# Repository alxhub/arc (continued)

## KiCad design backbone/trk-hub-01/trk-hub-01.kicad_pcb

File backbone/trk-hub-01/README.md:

# ARC-TRK-HUB-01

ARC-TRK-HUB-01 connects the ARC backbone to trackside devices. It receives commands over CAN and manages three separate LIN runs. Each run can serve signal and accessory nodes along the track and can be switched independently.

The hub has its own connection to the layout's supply. It measures the power sent down its LIN runs, so the controller can see their combined load. A status light and an expansion port are available at the hub.

The CAN backbone crosses an electrical isolation boundary here. The shorter LIN runs share the hub's local power and return.

[Board design](board.kdl)
[PCB layout](trk-hub-01.kicad_pcb)

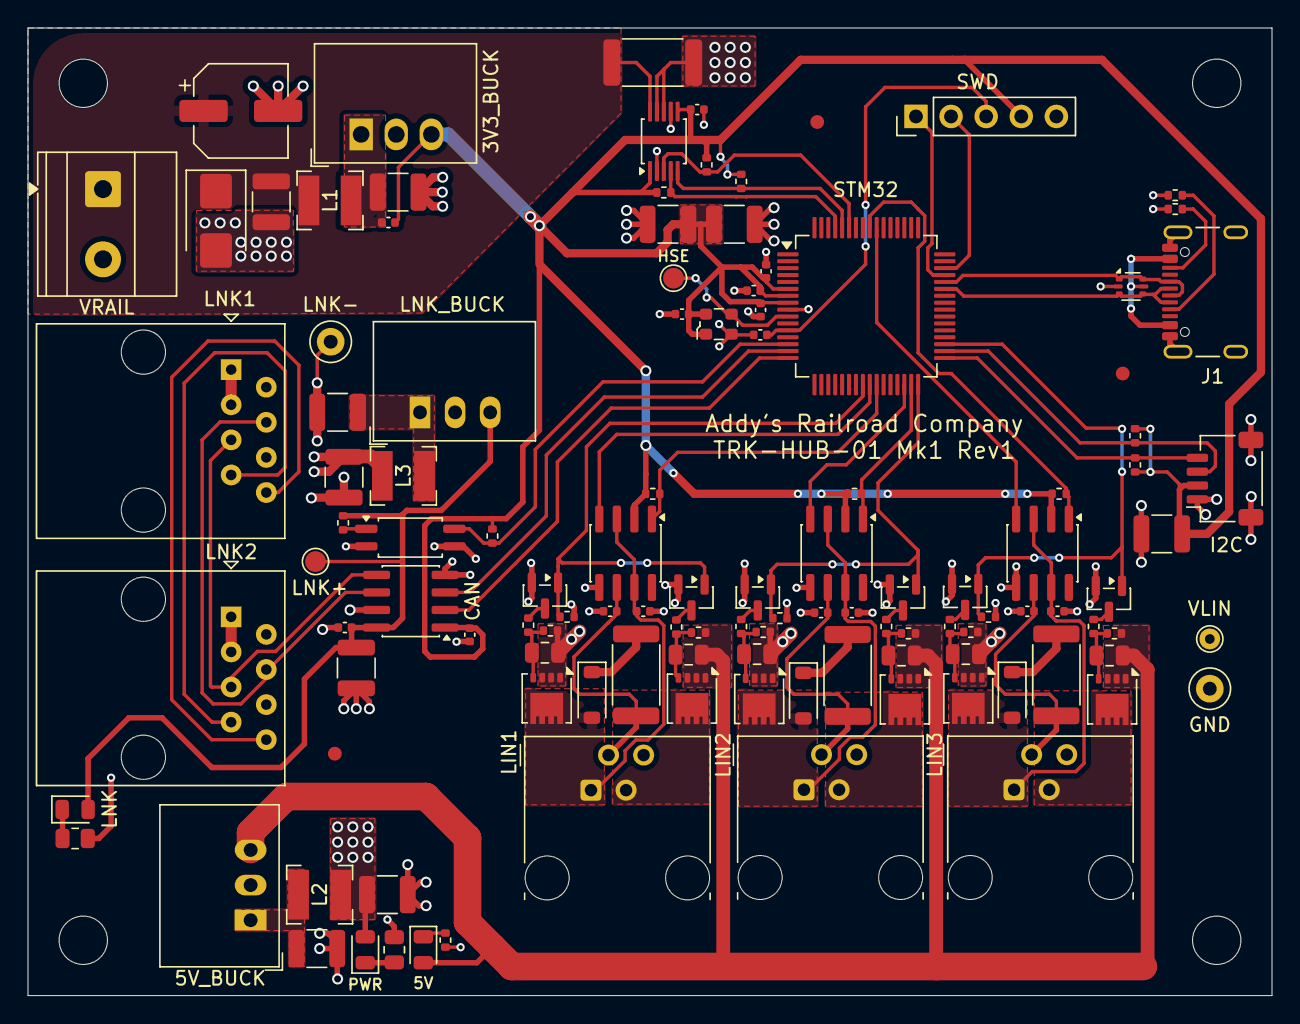
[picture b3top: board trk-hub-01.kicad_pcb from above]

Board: 4 copper layers, 90.0 x 70.0 mm, 121 parts (0 on the bottom side), 69 nets.

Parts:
3V3_BUCK: R-78K3.3-0.5; Converter_DCDC_RECOM_R-78K-0.5_THT
5V: green; LED_0805_2012Metric
5V_BUCK: R-78E5.0-0.5; Converter_DCDC_RECOM_R-78E-0.5_THT
C1: 47µF; CP_Elec_6.3x7.7
C2, C10, C14, C18, C22, C23, C25, C27, C28, C30, C31: 100nF; C_0402_1005Metric
C3, C4, C6, C20, C32: 10µF; C_1210_3225Metric
C5, C11, C15, C19: 1nF; C_0402_1005Metric
C7, C21, C24, C26: 4.7µF; C_1210_3225Metric
C8, C9, C12, C13, C16, C17: 1µF; C_0805_2012Metric
C29: 1µF; C_1210_3225Metric
CAN: ISO1044BD; SOIC-8_3.9x4.9mm_P1.27mm
D1: SMBJ18A; D_SMB
D2, D3, D4: 1N4148W; D_SOD-123
FID1, FID2, FID3: Fiducial; Fiducial_1mm_Mask2mm
GND: TestPoint; TestPoint_Loop_D2.50mm_Drill1.0mm
H1, H2, H3, H4: MountingHole; MountingHole_3.5mm
HSE: TestPoint; TestPoint_Pad_D1.5mm
I2C: Conn_01x04_MountingPin; JST_SH_SM04B-SRSS-TB_1x04-1MP_P1.00mm_Horizontal
J1: USB_C_Receptacle_USB2.0_16P; USB_C_Receptacle_GCT_USB4105-xx-A_16P_TopMnt_Horizontal
L1: 100µH; L_Bourns-SRN4018
L2, L3: 15µH; L_Bourns-SRN4018
LIN1, LIN2, LIN3: RJ11; RJ11_Stewart_SS-90000-006_Horizontal
LNK: green; LED_0805_2012Metric
LNK1, LNK2: RJ45; RJ45_Amphenol_54602-x08_Horizontal
LNK+: TestPoint; TestPoint_Pad_D1.5mm
LNK-: TestPoint; TestPoint_Loop_D2.50mm_Drill1.0mm
LNK_BUCK: R-78E5.0-0.5; Converter_DCDC_RECOM_R-78E-0.5_THT
MON: INA226; TSSOP-10_3x3mm_P0.5mm
PWR: green; LED_0805_2012Metric
Q1, Q3, Q5, Q7, Q9, Q11: DMP3013SFV; Diodes_PowerDI3333-8
Q2, Q4, Q6, Q8, Q10, Q12: BSS138; SOT-23
R1: 20mΩ; R_2512_6332Metric
R2: 1kΩ; R_0402_1005Metric
R3: 5.1kΩ; R_0805_2012Metric
R4: 300Ω; R_0402_1005Metric
R5, R8, R12, R15, R19, R22: 49.9kΩ; R_0402_1005Metric
R6, R9, R13, R16, R20, R23, R29, R30: 5.1kΩ; R_0402_1005Metric
R7, R14, R21, R28: 100kΩ; R_0402_1005Metric
R10, R17, R24: 10kΩ; R_0402_1005Metric
R11, R18, R25: 1kΩ; R_2512_6332Metric
R26: 300Ω; R_0805_2012Metric
R27: 2kΩ; R_0402_1005Metric
R31, R32, R33, R34: 4.7kΩ; R_0402_1005Metric
STM32: STM32G0B1RETx; LQFP-64_10x10mm_P0.5mm
SWD: Conn_01x05; PinHeader_1x05_P2.54mm_Vertical
U1, U2, U3: NCV7321D12R2G; SOIC-8_3.9x4.9mm_P1.27mm
U4: FODM217A; SOP-4_4.4x2.6mm_P1.27mm
U5: USBLC6-2P6; SOT-666
VLIN: TestPoint; TestPoint_THTPad_D1.5mm_Drill0.7mm
VRAIL: Conn_01x02; TerminalBlock_Phoenix_MKDS-1,5-2-5.08_1x02_P5.08mm_Horizont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
Y1: 40MHz; Oscillator_SMD_ECS_2520MV-xxx-xx-4Pin_2.5x2.0mm

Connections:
3V3: 3V3_BUCK.3, C2.1, C5.2, C22.1, C25.1, C26.1, C28.1, C29.1, C30.1, C31.1, C32.1, CAN.1, I2C.2, MON.1, MON.6, R2.2, R10.2, R17.2, R24.2, R28.2, R31.2, R32.2, R33.2, R34.2, STM32.6, STM32.7, STM32.8, SWD.4, U1.2, U2.2, U3.2, Y1.1, Y1.4
unnamed: 3V3_BUCK.1, C4.1, C5.1, L1.2
unnamed: 5V.1, R4.1
unnamed: 5V_BUCK.1, C7.1, L2.2
unnamed: LNK.1, R26.1
unnamed: C21.1, L3.2, LNK_BUCK.1
unnamed: PWR.1, R3.1
unnamed: R27.2, U4.1
V5: 5V.2, 5V_BUCK.3, C9.2, C13.2, C17.2, Q3.1, Q3.2, Q3.3, Q7.1, Q7.2, Q7.3, Q11.1, Q11.2, Q11.3, R8.2, R15.2, R22.2
VBUS: J1.A4, J1.A9, J1.B4, J1.B9, U5.5
can/rxd: CAN.3, STM32.15
can/txd: CAN.2, STM32.16
expansion/scl: I2C.4, R34.1, STM32.33
expansion/sda: I2C.3, R33.1, STM32.34
hse: HSE.1, STM32.10, Y1.3
leg0/EN: Q2.1, Q4.1, R7.1, STM32.24
leg0/LIN: C11.1, LIN1.2, R11.2, U1.6
leg0/V5: LIN1.3, Q3.5
leg0/VPWR: C10.1, D2.2, LIN1.1, Q1.5, U1.3, U1.7
leg0/rxd: R10.1, STM32.26, U1.1
leg0/switch5/GATE: C9.1, Q3.4, R8.1, R9.2
leg0/switch5/drive: Q4.3, R9.1
leg0/switch/GATE: C8.1, Q1.4, R5.1, R6.2
leg0/switch/drive: Q2.3, R6.1
leg0/term/K: D2.1, R11.1
leg0/txd: STM32.25, U1.4
leg1/EN: Q6.1, Q8.1, R14.1, STM32.32
leg1/LIN: C15.1, LIN2.2, R18.2, U2.6
leg1/V5: LIN2.3, Q7.5
leg1/VPWR: C14.1, D3.2, LIN2.1, Q5.5, U2.3, U2.7
leg1/rxd: R17.1, STM32.31, U2.1
leg1/switch5/GATE: C13.1, Q7.4, R15.1, R16.2
leg1/switch5/drive: Q8.3, R16.1
leg1/switch/GATE: C12.1, Q5.4, R12.1, R13.2
leg1/switch/drive: Q6.3, R13.1
leg1/term/K: D3.1, R18.1
leg1/txd: STM32.30, U2.4
leg2/EN: Q10.1, Q12.1, R21.1, STM32.35
leg2/LIN: C19.1, LIN3.2, R25.2, U3.6
leg2/V5: LIN3.3, Q11.5
leg2/VPWR: C18.1, D4.2, LIN3.1, Q9.5, U3.3, U3.7
leg2/rxd: R24.1, STM32.56, U3.1
leg2/switch5/GATE: C17.1, Q11.4, R22.1, R23.2
leg2/switch5/drive: Q12.3, R23.1
leg2/switch/GATE: C16.1, Q9.4, R19.1, R20.2
leg2/switch/drive: Q10.3, R20.1
leg2/term/K: D4.1, R25.1
leg2/txd: STM32.55, U3.4
link/V5_LINK: C23.1, C24.1, CAN.8, LNK.2, LNK+.1, LNK_BUCK.3, R27.1
link/VLINK: C20.1, L3.1, LNK1.1, LNK1.3, LNK2.1, LNK2.3
link/VLINK_GND: C20.2, C21.2, C23.2, C24.2, CAN.7, LNK1.2, LNK1.6, LNK2.2, LNK2.6, LNK-.1, LNK_BUCK.2, R26.2, U4.2
link/good: R28.1, STM32.14, U4.4
link/jacks/CANH: CAN.6, LNK1.4, LNK2.4
link/jacks/CANL: CAN.5, LNK1.5, LNK2.5
link/jacks/DCC_A: LNK1.7, LNK2.7
link/jacks/DCC_B: LNK1.8, LNK2.8
monitor/scl: MON.5, R32.1, STM32.60
monitor/sda: MON.4, R31.1, STM32.61
nALERT: MON.3, R2.1, STM32.59
nrst: C27.1, STM32.12, SWD.3
rail/GND: 3V3_BUCK.2, 5V_BUCK.2, C1.2, C2.2, C3.2, C4.2, C6.2, C7.2, C10.2, C11.2, C14.2, C15.2, C18.2, C19.2, C22.2, C25.2, C26.2, C27.2, C28.2, C29.2, C30.2, C31.2, C32.2, CAN.4, D1.2, GND.1, I2C.1, I2C.MP, J1.A1, J1.A12, J1.B1, J1.B12, J1.SH, LIN1.4, LIN2.4, LIN3.4, MON.2, MON.7, Q2.2, Q4.2, Q6.2, Q8.2, Q10.2, Q12.2, R3.2, R4.2, R7.2, R14.2, R21.2, R29.2, R30.2, STM32.9, SWD.5, U1.5, U2.5, U3.5, U4.3, U5.2, VRAIL.2, Y1.2
rail/VLIN: C6.1, C8.2, C12.2, C16.2, L2.1, MON.8, MON.9, PWR.2, Q1.1, Q1.2, Q1.3, Q5.1, Q5.2, Q5.3, Q9.1, Q9.2, Q9.3, R1.2, R5.2, R12.2, R19.2, VLIN.1
rail/VPWR: C1.1, C3.1, D1.1, L1.1, MON.10, R1.1, VRAIL.1
swd/swclk: STM32.46, SWD.2
swd/swdio: STM32.45, SWD.1
usb/cc1: J1.A5, R29.1
usb/cc2: J1.B5, R30.1
usb/d+: J1.A6, J1.B6, STM32.44, U5.1, U5.6
usb/d-: J1.A7, J1.B7, STM32.43, U5.3, U5.4

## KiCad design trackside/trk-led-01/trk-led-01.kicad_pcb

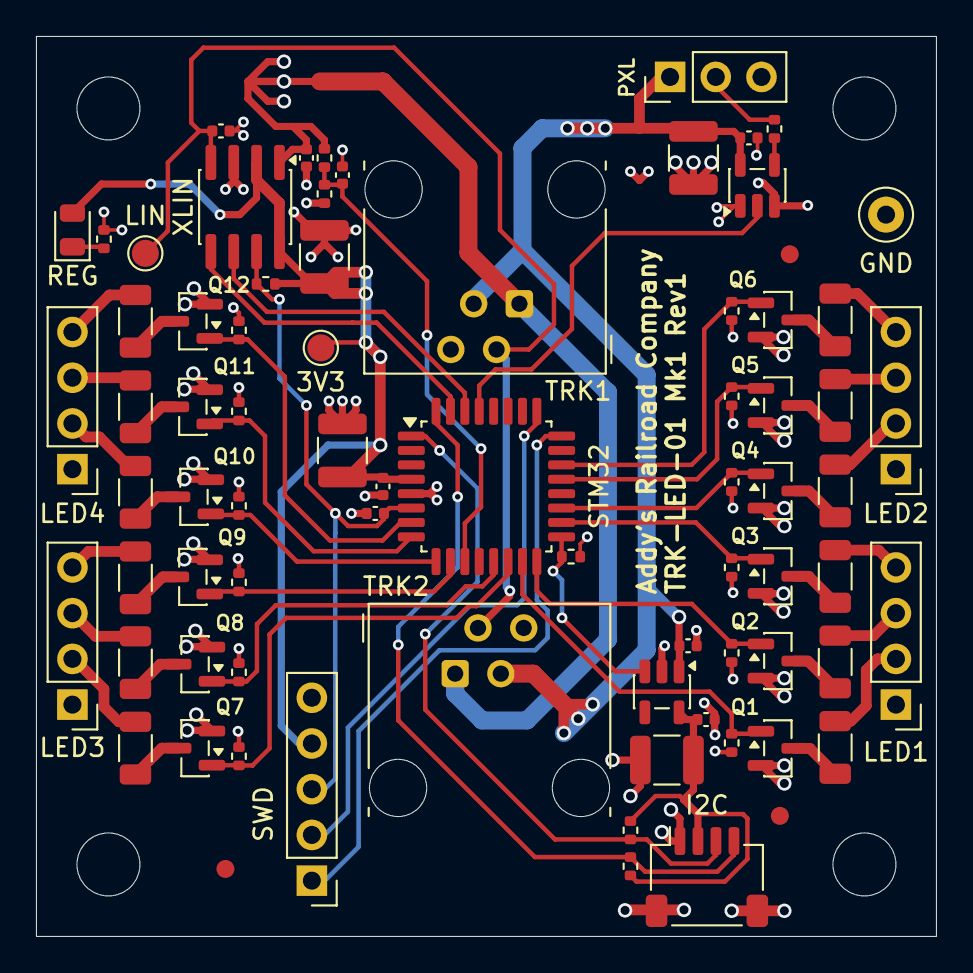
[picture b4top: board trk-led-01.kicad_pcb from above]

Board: 4 copper layers, 50.0 x 50.0 mm, 80 parts (0 on the bottom side), 55 nets.

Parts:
3V3: TestPoint; TestPoint_Pad_D1.5mm
C1, C4, C6, C7, C9: 100nF; C_0402_1005Metric
C2, C5, C12: 10µF; C_1210_3225Metric
C3: 220pF; C_0402_1005Metric
C8: 4.7µF; C_1210_3225Metric
C10, C11: 1µF; C_0402_1005Metric
FID1, FID2, FID3: Fiducial; Fiducial_1mm_Mask2mm
GND: TestPoint; TestPoint_Loop_D2.50mm_Drill1.0mm
H1, H2, H3, H4: MountingHole; MountingHole_3.5mm
I2C: Conn_01x04_MountingPin; JST_SH_SM04B-SRSS-TB_1x04-1MP_P1.00mm_Horizontal
LED1, LED2, LED3, LED4: Conn_01x04; PinHeader_1x04_P2.54mm_Vertical
LIN: TestPoint; TestPoint_Pad_D1.5mm
PXL: Conn_01x03; PinHeader_1x03_P2.54mm_Vertical
Q1, Q2, Q3, Q4, Q5, Q6, Q7, Q8, Q9, Q10, Q11, Q12: DMN3404L; SOT-23
R1: 10kΩ; R_0402_1005Metric
R2: 330Ω; R_0402_1005Metric
R3, R5, R7, R9, R11, R13, R15, R17, R19, R21, R23, R25, R27, R30: 100kΩ; R_0402_1005Metric
R4, R6, R8, R10, R12, R14, R16, R18, R20, R22, R24, R26: 4.3kΩ; R_1206_3216Metric
R28: 18kΩ; R_0402_1005Metric
R29: 680Ω; R_0402_1005Metric
R31, R32: 4.7kΩ; R_0402_1005Metric
REG: green; LED_0805_2012Metric
STM32: STM32C092KBTx; LQFP-32_7x7mm_P0.8mm
SWD: Conn_01x05; PinHeader_1x05_P2.54mm_Vertical
TRK1, TRK2: RJ11; RJ11_Stewart_SS-90000-006_Horizontal
U1: 74AHCT1G125; SOT-23-5
U2: AP2112K-3.3; SOT-23-5
XLIN: NCV7428D13R2G; SOIC-8_3.9x4.9mm_P1.27mm

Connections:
unnamed: R29.1, REG.1
unnamed: R2.1, U1.4
unnamed: R30.1, STM32.17, U2.3
debug/swd.swclk: STM32.25, SWD.2
debug/swd.swdio: STM32.24, SWD.1
expansion/pulls/i2c.scl: I2C.4, R32.1, STM32.32
expansion/pulls/i2c.sda: I2C.3, R31.1, STM32.1
expansion/pulls/rail.rail: C11.1, C12.1, I2C.2, R31.2, R32.2, U2.5
head1/K1: LED1.2, R4.2
head1/K2: LED1.3, R6.2
head1/K3: LED1.4, R8.2
head1/gates.l1: Q1.1, R3.1, STM32.15
head1/gates.l2: Q2.1, R5.1, STM32.16
head1/gates.l3: Q3.1, R7.1, STM32.18
head1/l1/drain: Q1.3, R4.1
head1/l2/drain: Q2.3, R6.1
head1/l3/drain: Q3.3, R8.1
head2/K1: LED2.2, R10.2
head2/K2: LED2.3, R12.2
head2/K3: LED2.4, R14.2
head2/gates.l1: Q4.1, R9.1, STM32.19
head2/gates.l2: Q5.1, R11.1, STM32.21
head2/gates.l3: Q6.1, R13.1, STM32.22
head2/l1/drain: Q4.3, R10.1
head2/l2/drain: Q5.3, R12.1
head2/l3/drain: Q6.3, R14.1
head3/K1: LED3.2, R16.2
head3/K2: LED3.3, R18.2
head3/K3: LED3.4, R20.2
head3/gates.l1: Q7.1, R15.1, STM32.14
head3/gates.l2: Q8.1, R17.1, STM32.13
head3/gates.l3: Q9.1, R19.1, STM32.10
head3/l1/drain: Q7.3, R16.1
head3/l2/drain: Q8.3, R18.1
head3/l3/drain: Q9.3, R20.1
head4/K1: LED4.2, R22.2
head4/K2: LED4.3, R24.2
head4/K3: LED4.4, R26.2
head4/gates.l1: Q10.1, R21.1, STM32.9
head4/gates.l2: Q11.1, R23.1, STM32.8
head4/gates.l3: Q12.1, R25.1, STM32.7
head4/l1/drain: Q10.3, R22.1
head4/l2/drain: Q11.3, R24.1
head4/l3/drain: Q12.3, R26.1
node/GND: C1.2, C2.2, C3.2, C4.2, C5.2, C6.2, C7.2, C8.2, C9.2, C10.2, C11.2, C12.2, GND.1, I2C.1, I2C.MP, PXL.3, Q1.2, Q2.2, Q3.2, Q4.2, Q5.2, Q6.2, Q7.2, Q8.2, Q9.2, Q10.2, Q11.2, Q12.2, R3.2, R5.2, R7.2, R9.2, R11.2, R13.2, R15.2, R17.2, R19.2, R21.2, R23.2, R25.2, R28.2, R29.2, R30.2, STM32.5, SWD.5, TRK1.4, TRK2.4, U1.1, U1.3, U2.2, XLIN.3
node/LIN: C3.1, LIN.1, TRK1.2, TRK2.2, XLIN.4
node/V5: C4.1, C5.1, C10.1, PXL.1, TRK1.3, TRK2.3, U1.5, U2.1
node/VPWR: C1.1, LED1.1, LED2.1, LED3.1, LED4.1, R27.1, TRK1.1, TRK2.1, XLIN.1
node/link.rx: STM32.30, XLIN.6
node/link.tx: STM32.31, XLIN.5
node/v3v3.rail: 3V3.1, C2.1, C7.1, C8.1, R1.2, REG.2, STM32.4, SWD.4, XLIN.2, XLIN.8
nrst: C9.1, R1.1, STM32.6, SWD.3, XLIN.7
pixels/DOUT: PXL.2, R2.2
pixels/data: STM32.29, U1.2
sense/tap: C6.1, R27.2, R28.1, STM32.11

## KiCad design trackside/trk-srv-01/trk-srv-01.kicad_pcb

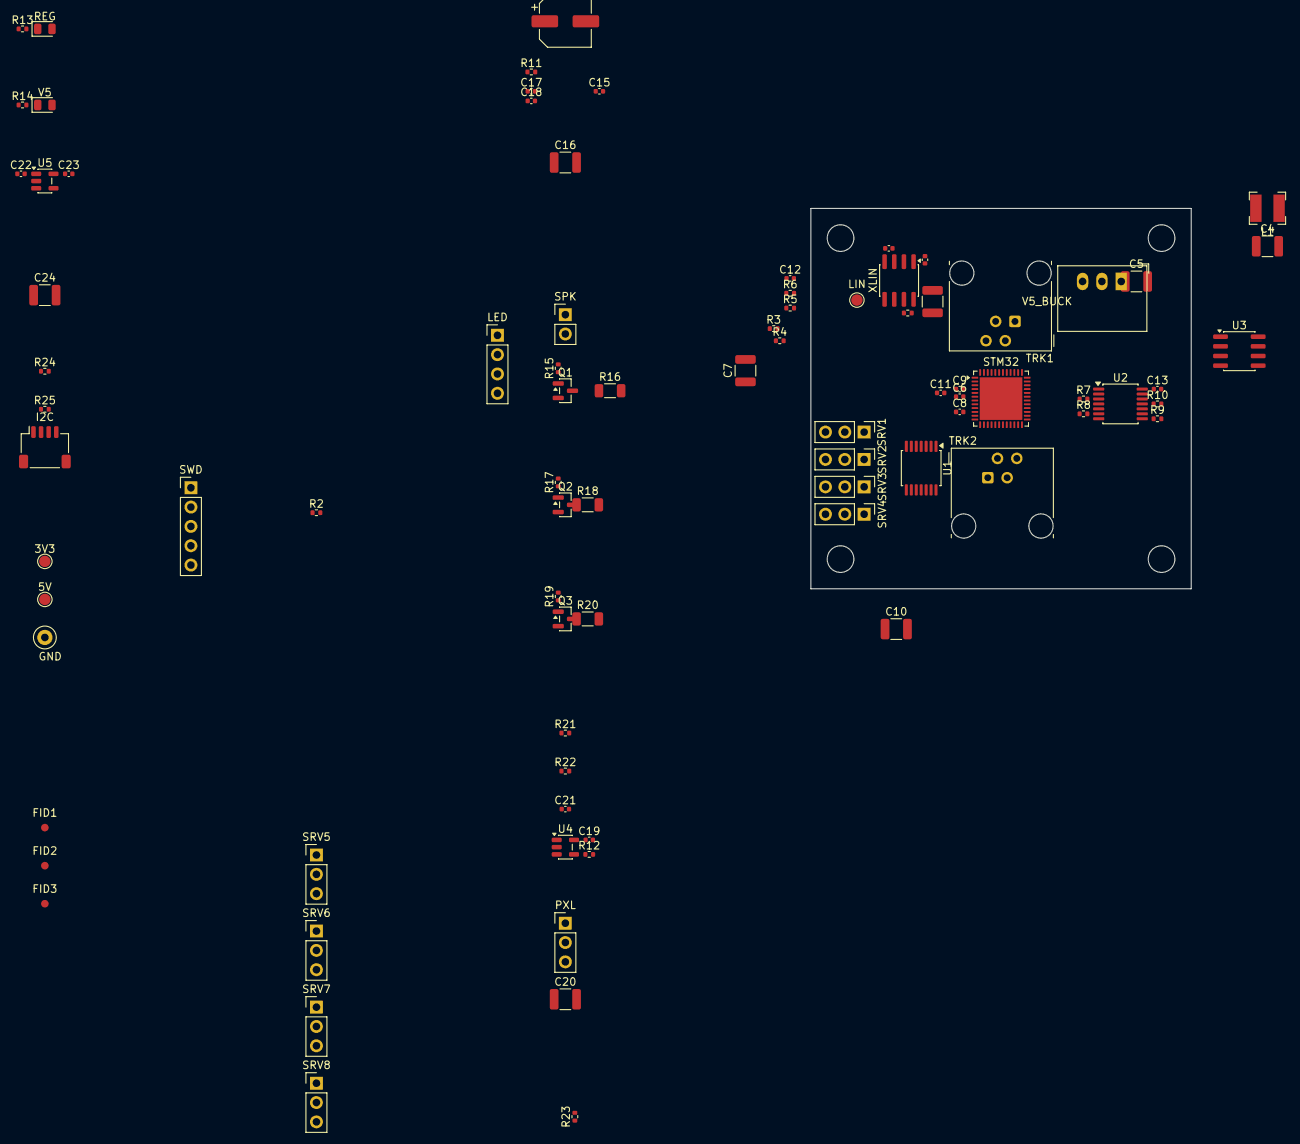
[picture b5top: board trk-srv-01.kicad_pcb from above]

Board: 2 copper layers, 50.0 x 50.0 mm, 89 parts (0 on the bottom side), 54 nets, no tracks yet.

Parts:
3V3, 5V: TestPoint; TestPoint_Pad_D1.5mm
C1, C6, C8, C9, C11, C12, C13, C17, C18, C19, C21: 100nF; C_0402_1005Metric
C2, C4, C5, C16, C20, C24: 10µF; C_1210_3225Metric
C3: 220pF; C_0402_1005Metric
C7: 4.7µF; C_1210_3225Metric
C10: 1µF; C_1210_3225Metric
C14: 100µF; CP_Elec_6.3x5.8
C15, C22, C23: 1µF; C_0402_1005Metric
FID1, FID2, FID3: Fiducial; Fiducial_1mm_Mask2mm
GND: TestPoint; TestPoint_Loop_D2.50mm_Drill1.0mm
H1, H2, H3, H4: MountingHole; MountingHole_3.5mm
I2C: Conn_01x04_MountingPin; JST_SH_SM04B-SRSS-TB_1x04-1MP_P1.00mm_Horizontal
L1: 15µH; L_Bourns-SRN4018
LED: Conn_01x04; PinHeader_1x04_P2.54mm_Vertical
LIN: TestPoint; TestPoint_Pad_D1.5mm
PXL: Conn_01x03; PinHeader_1x03_P2.54mm_Vertical
Q1, Q2, Q3: DMN3404L; SOT-23
R1: 10kΩ; R_0402_1005Metric
R2, R3, R4, R5, R6, R7, R8, R9, R10, R11, R15, R17, R19, R21, R23: 100kΩ; R_0402_1005Metric
R12: 330Ω; R_0402_1005Metric
R13: 680Ω; R_0402_1005Metric
R14: 1.5kΩ; R_0402_1005Metric
R16, R18, R20: 4.3kΩ; R_1206_3216Metric
R22: 18kΩ; R_0402_1005Metric
R24, R25: 4.7kΩ; R_0402_1005Metric
REG: green; LED_0805_2012Metric
SPK: Conn_01x02; PinHeader_1x02_P2.54mm_Vertical
SRV1, SRV2, SRV3, SRV4, SRV5, SRV6, SRV7, SRV8: Conn_01x03; PinHeader_1x03_P2.54mm_Vertical
STM32: STM32G0B1CEUx; QFN-48-1EP_7x7mm_P0.5mm_EP5.6x5.6mm
SWD: Conn_01x05; PinHeader_1x05_P2.54mm_Vertical
TRK1, TRK2: RJ11; RJ11_Stewart_SS-90000-006_Horizontal
U1, U2: 74AHCT125; TSSOP-14_4.4x5mm_P0.65mm
U3: PAM8302AAD; SOIC-8_3.9x4.9mm_P1.27mm
U4: 74AHCT1G125; SOT-23-5
U5: AP2112K-3.3; SOT-23-5
V5: green; LED_0805_2012Metric
V5_BUCK: R-78E5.0-1.0; Converter_DCDC_RECOM_R-78E-0.5_THT
XLIN: NCV7428D13R2G; SOIC-8_3.9x4.9mm_P1.27mm

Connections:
unnamed: R13.1, REG.1
unnamed: R3.1, SRV1.1, U1.3
unnamed: R4.1, SRV2.1, U1.6
unnamed: R5.1, SRV3.1, U1.8
unnamed: R6.1, SRV4.1, U1.11
unnamed: R7.1, SRV5.1, U2.3
unnamed: R8.1, SRV6.1, U2.6
unnamed: R9.1, SRV7.1, U2.8
unnamed: R10.1, SRV8.1, U2.11
unnamed: C17.2, U3.3
unnamed: C18.2, U3.4
unnamed: R12.1, U4.4
unnamed: R23.1, STM32.21, U5.3
unnamed: R14.1, V5.1
bell/OUT+: SPK.1, U3.5
bell/OUT-: SPK.2, U3.8
bell/enable: R11.1, STM32.25, U3.1
bell/in: C17.1, STM32.15
expansion/pulls/i2c.scl: I2C.4, R25.1, STM32.47
expansion/pulls/i2c.sda: I2C.3, R24.1, STM32.48
expansion/pulls/rail.rail: C23.1, C24.1, I2C.2, R24.2, R25.2, U5.5
lamp1/drain: Q1.3, R16.1
lamp1/gate: Q1.1, R15.1, STM32.28
lamp2/drain: Q2.3, R18.1
lamp2/gate: Q2.1, R17.1, STM32.29
lamp3/drain: Q3.3, R20.1
lamp3/gate: Q3.1, R19.1, STM32.32
lamps/K1: LED.2, R16.2
lamps/K2: LED.3, R18.2
lamps/K3: LED.4, R20.2
lin/rxd: STM32.46, XLIN.5
lin/txd: STM32.45, XLIN.6
node/GND: C1.2, C2.2, C3.2, C4.2, C5.2, C6.2, C7.2, C8.2, C9.2, C10.2, C11.2, C12.2, C13.2, C14.2, C15.2, C16.2, C18.1, C19.2, C20.2, C21.2, C22.2, C23.2, C24.2, GND.1, I2C.1, I2C.MP, PXL.3, Q1.2, Q2.2, Q3.2, R3.2, R4.2, R5.2, R6.2, R7.2, R8.2, R9.2, R10.2, R11.2, R13.2, R14.2, R15.2, R17.2, R19.2, R22.2, R23.2, SRV1.3, SRV2.3, SRV3.3, SRV4.3, SRV5.3, SRV6.3, SRV7.3, SRV8.3, STM32.7, STM32.49, SWD.5, TRK1.4, TRK2.4, U1.7, U2.7, U3.7, U4.1, U4.3, U5.2, V5_BUCK.2, XLIN.3
node/LIN: C3.1, LIN.1, TRK1.2, TRK2.2, XLIN.4
node/V5: TRK1.3, TRK2.3
node/VPWR: C1.1, C4.1, L1.1, LED.1, R21.1, TRK1.1, TRK2.1, XLIN.1
node/v3v3.rail: 3V3.1, C2.1, C6.1, C7.1, C9.1, C10.1, C11.1, R1.2, REG.2, STM32.4, STM32.5, STM32.6, SWD.4, XLIN.2, XLIN.8
nrst: C8.1, R1.1, STM32.10, SWD.3, XLIN.7
pixels/DOUT: PXL.2, R12.2
pixels/data: STM32.44, U4.2
sense/tap: C21.1, R21.2, R22.1, STM32.22
servos/enable: R2.1, STM32.24, U1.1, U1.4, U1.10, U1.13, U2.1, U2.4, U2.10, U2.13
servos/p1: STM32.11, U1.2
servos/p2: STM32.12, U1.5
servos/p3: STM32.13, U1.9
servos/p4: STM32.14, U1.12
servos/p5: STM32.17, U2.2
servos/p6: STM32.18, U2.5
servos/p7: STM32.19, U2.9
servos/p8: STM32.20, U2.12
swd/swd.swclk: STM32.36, SWD.2
swd/swd.swdio: STM32.35, SWD.1
v5/filtered.rail: C5.1, L1.2, V5_BUCK.1
v5/out.rail: 5V.1, C12.1, C13.1, C14.1, C15.1, C16.1, C19.1, C20.1, C22.1, PXL.1, R2.2, SRV1.2, SRV2.2, SRV3.2, SRV4.2, SRV5.2, SRV6.2, SRV7.2, SRV8.2, U1.14, U2.14, U3.6, U4.5, U5.1, V5.2, V5_BUCK.3

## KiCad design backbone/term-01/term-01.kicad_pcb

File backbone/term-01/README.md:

# ARC-TERM-01

ARC-TERM-01 closes the end of an ARC backbone run. It terminates both the CAN connection used for commands and status and the DCC timing connection used by track drivers. A run uses a terminator at each end; the nodes along it pass the connections through.

The board has one backbone jack. A power light shows whether the backbone supply reaches this end of the run, and measurement points give installers a place to check the supply and both signal pairs.

[Board design](board.kdl)
[PCB layout](term-01.kicad_pcb)

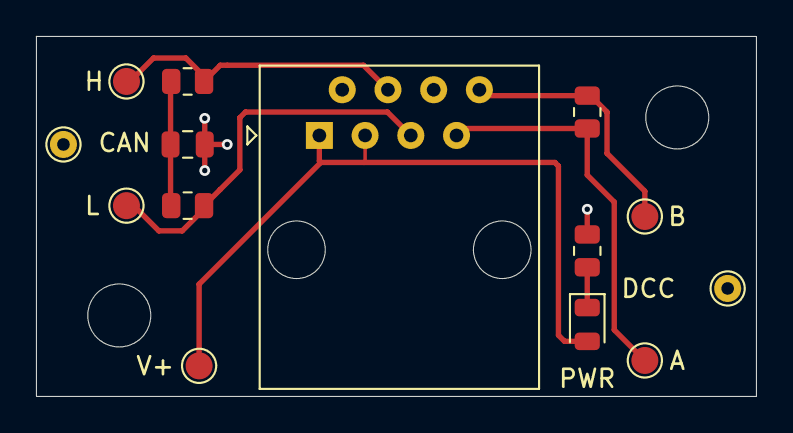
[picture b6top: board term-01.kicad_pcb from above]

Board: 2 copper layers, 40.0 x 20.0 mm, 16 parts (0 on the bottom side), 8 nets.

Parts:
A: TestPoint; TestPoint_Pad_D1.5mm
B: TestPoint; TestPoint_Pad_D1.5mm
C1: 4.7nF; C_0805_2012Metric
H: TestPoint; TestPoint_Pad_D1.5mm
H1, H2: MountingHole; MountingHole_3.5mm
L: TestPoint; TestPoint_Pad_D1.5mm
LNK: RJ45; RJ45_Amphenol_54602-x08_Horizontal
PWR: green; LED_0805_2012Metric
R1, R2: 62Ω; R_0805_2012Metric
R3: 120Ω; R_0805_2012Metric
R4: 5.1kΩ; R_0805_2012Metric
TP1, TP2: TestPoint; TestPoint_THTPad_D1.5mm_Drill0.7mm
V+: TestPoint; TestPoint_Pad_D1.5mm

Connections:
CANH: H.1, LNK.4, R1.1
CANL: L.1, LNK.5, R2.2
CAN_MID: C1.1, R1.2, R2.1
DCC_A: A.1, LNK.7, R3.1
DCC_B: B.1, LNK.8, R3.2
unnamed: PWR.1, R4.1
entry/VLINK: LNK.1, LNK.3, PWR.2, V+.1
entry/VLINK_GND: C1.2, LNK.2, LNK.6, R4.2, TP1.1, TP2.1

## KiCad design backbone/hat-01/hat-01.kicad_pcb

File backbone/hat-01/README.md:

# ARC-HAT-01

ARC-HAT-01 connects a Raspberry Pi to an ARC layout. It powers the Pi from the cabinet's control supply, gives Linux a CAN interface to the backbone, and lets the Pi listen to DCC timing. The Pi controls the layout's master contactor and reads its auxiliary contact to learn whether the contactor closed.

The HAT also exposes the Pi's I²C bus on a Qwiic connector. It keeps the backbone electrically isolated from the Pi and cabinet control wiring.

[Board design](board.kdl)
[PCB layout](hat-01.kicad_pcb)

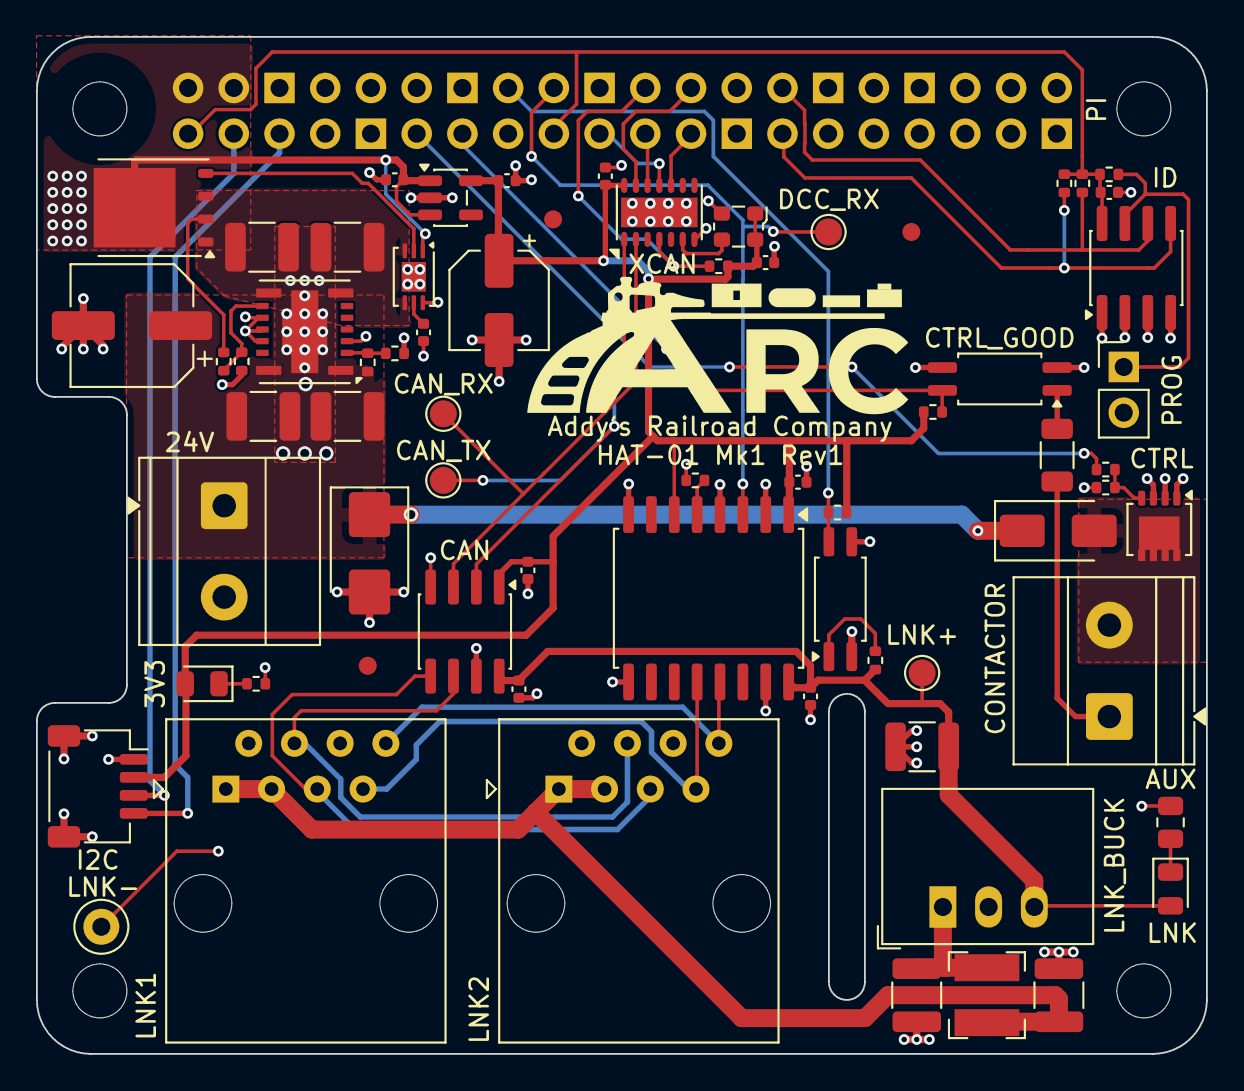
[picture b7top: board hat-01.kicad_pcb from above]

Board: 4 copper layers, 65.0 x 56.5 mm, 69 parts (0 on the bottom side), 43 nets.

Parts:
3V3: green; LED_0805_2012Metric
24V: Conn_01x02; TerminalBlock_Phoenix_MKDS-1,5-2-5.08_1x02_P5.08mm_Horizont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
C1, C11, C12, C15, C16, C18, C19: 100nF; C_0402_1005Metric
C2: 47µF; CP_Elec_6.3x7.7
C3, C4, C13: 10µF; C_1210_3225Metric
C5, C6: 47µF; C_1210_3225Metric
C7: 10nF; C_0402_1005Metric
C8, C9: 1µF; C_0402_1005Metric
C10: 10µF; CP_Elec_5x5.8
C14, C17: 4.7µF; C_1210_3225Metric
CAN: ISO1044BD; SOIC-8_3.9x4.9mm_P1.27mm
CAN_RX: TestPoint; TestPoint_Pad_D1.5mm
CAN_TX: TestPoint; TestPoint_Pad_D1.5mm
CONTACTOR: Conn_01x02; TerminalBlock_Phoenix_MKDS-1,5-2-5.08_1x02_P5.08mm_Horizont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
CTRL: BUK9M53-60EX; LFPAK33
CTRL_GOOD: FODM217A; SOP-4_4.4x2.6mm_P1.27mm
D1: SMBJ26A; D_SMB
D2: SS16; D_SMA
DCC_RX: TestPoint; TestPoint_Pad_D1.5mm
DCC_SYNC: ISO1430DW; SOIC-16W_7.5x10.3mm_P1.27mm
FID1, FID2, FID3: Fiducial; Fiducial_1mm_Mask2mm
I2C: Conn_01x04_MountingPin; JST_SH_SM04B-SRSS-TB_1x04-1MP_P1.00mm_Horizontal
ID: CAT24C256; SOIC-8_3.9x4.9mm_P1.27mm
L1: 15µH; L_Bourns-SRN4018
LNK: green; LED_0805_2012Metric
LNK1, LNK2: RJ45; RJ45_Amphenol_54602-x08_Horizontal
LNK+: TestPoint; TestPoint_Pad_D1.5mm
LNK-: TestPoint; TestPoint_Loop_D2.50mm_Drill1.0mm
LNK_BUCK: R-78E5.0-0.5; Converter_DCDC_RECOM_R-78E-0.5_THT
PI: RPi_GPIO; RPI_Hat_B+
PROG: Conn_01x02; PinHeader_1x02_P2.54mm_Vertical
Q1: BSC030N08NS5; TDSON-8-1
R1, R4, R11, R15: 10kΩ; R_0402_1005Metric
R2, R3, R9: 4.7kΩ; R_0402_1005Metric
R5: 2.44kΩ; R_0402_1005Metric
R6, R13, R17: 100kΩ; R_0402_1005Metric
R7: 6.92kΩ; R_0402_1005Metric
R8: 680Ω; R_0402_1005Metric
R10: 300Ω; R_0805_2012Metric
R12: 2kΩ; R_0402_1005Metric
R14: 100Ω; R_0402_1005Metric
R16: 4.3kΩ; R_1206_3216Metric
U1: TPSM53603RDA; Texas_B3QFN-14-1EP_5x5.5mm_P0.65mm
U2: LTC4359-DCB; DFN-6-1EP_3x2mm_P0.5mm_EP1.65x1.35mm
U3: AP2112K-3.3; SOT-23-5
U4: FODM217A; SOP-4_4.4x2.6mm_P1.27mm
XCAN: MCP2518FD-xQBB; DFN-14-1EP_3x4.5mm_P0.65mm_EP1.65x4.25mm
Y1: 40MHz; Oscillator_SMD_ECS_2520MV-xxx-xx-4Pin_2.5x2.0mm

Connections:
3V3: 3V3.2, C9.1, C10.1, C11.1, C12.1, C15.1, C18.1, CAN.1, DCC_SYNC.1, DCC_SYNC.6, I2C.2, R9.2, R13.2, R17.2, U3.5, XCAN.14, Y1.1, Y1.4
unnamed: 3V3.1, R8.1
unnamed: CONTACTOR.1, R16.1
unnamed: CONTACTOR.2, CTRL.5, D2.2
unnamed: CTRL.4, R14.2, R15.1
unnamed: CTRL_GOOD.1, R16.2
unnamed: ID.7, PROG.1, R1.1
unnamed: LNK.1, R10.1
unnamed: C14.1, L1.2, LNK_BUCK.1
unnamed: R6.2, R7.1, U1.2
unnamed: R4.2, R5.1, U1.9
unnamed: Q1.4, U2.2
unnamed: C7.1, U2.5
unnamed: R12.2, U4.1
unnamed: XCAN.6, Y1.3
V5: C8.1, PI.2, PI.4, Q1.5, U2.1, U3.1, U3.3
VCC_ID: C1.1, ID.8, PI.1, PI.17, R1.2, R2.2, R3.2
VCTL: 24V.1, C2.1, C3.1, C4.1, D1.1, D2.1, R6.1, U1.1, U1.14
buck/out.rail: C5.1, C6.1, Q1.1, Q1.2, Q1.3, R4.1, U1.7, U1.8, U2.3, U2.4
host/can-int: PI.22, R9.1, XCAN.4
host/contactor-aux: CTRL_GOOD.4, PI.13, R17.1
host/contactor-en: PI.11, R14.1
host/dcc-rxd: DCC_RX.1, DCC_SYNC.3, PI.18
host/id-power.gnd: 24V.2, C1.2, C2.2, C3.2, C4.2, C5.2, C6.2, C7.2, C8.2, C9.2, C10.2, C11.2, C12.2, C15.2, C18.2, CAN.4, CTRL.1, CTRL.2, CTRL.3, CTRL_GOOD.2, CTRL_GOOD.3, D1.2, DCC_SYNC.2, DCC_SYNC.4, DCC_SYNC.8, I2C.1, I2C.MP, ID.1, ID.2, ID.3, ID.4, PI.6, PI.9, PI.14, PI.20, PI.25, PI.30, PI.34, PI.39, PROG.2, R5.2, R7.2, R8.2, R11.2, R15.2, U1.3, U1.10, U1.11, U1.12, U1.15, U2.6, U2.7, U3.2, U4.3, XCAN.7, XCAN.15, Y1.2
host/id/i2c.scl: ID.6, PI.28, R3.1
host/id/i2c.sda: ID.5, PI.27, R2.1
host/link-good: PI.16, R13.1, U4.4
host/scl: I2C.4, PI.5
host/sda: I2C.3, PI.3
host/spi-cs: PI.24, XCAN.13
host/spi-miso: PI.21, XCAN.12
host/spi-mosi: PI.19, XCAN.11
host/spi-sck: PI.23, XCAN.10
link/V5_LINK: C16.1, C17.1, C19.1, CAN.8, DCC_SYNC.16, LNK.2, LNK+.1, LNK_BUCK.3, R12.1
link/VLINK: C13.1, L1.1, LNK1.1, LNK1.3, LNK2.1, LNK2.3
link/VLINK_GND: C13.2, C14.2, C16.2, C17.2, C19.2, CAN.7, DCC_SYNC.9, DCC_SYNC.15, LNK1.2, LNK1.6, LNK2.2, LNK2.6, LNK-.1, LNK_BUCK.2, R10.2, U4.2
link/dcc-de: DCC_SYNC.5, R11.1
link/fdcan.rx: CAN.3, CAN_RX.1, XCAN.2
link/fdcan.tx: CAN.2, CAN_TX.1, XCAN.1
link/jacks/CANH: CAN.6, LNK1.4, LNK2.4
link/jacks/CANL: CAN.5, LNK1.5, LNK2.5
link/jacks/DCC_A: DCC_SYNC.12, LNK1.7, LNK2.7
link/jacks/DCC_B: DCC_SYNC.13, LNK1.8, LNK2.8

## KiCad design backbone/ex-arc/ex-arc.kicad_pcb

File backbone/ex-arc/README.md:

# ARC-EX-ARC

ARC-EX-ARC fits between a CommandStation-EX CSB1 and its motor shield. It lets the command station join ARC's CAN backbone and share its DCC timing with other districts. When the CSB1 acts as a booster, the board can feed it the backbone's DCC timing instead.

A small controller handles backbone communication, selects the booster input, and watches the motor shield's fault outputs. It can brake either track channel locally and tell the CSB1 what happened over a dedicated UART.

[Board design](board.kdl)
[PCB layout](ex-arc.kicad_pcb)

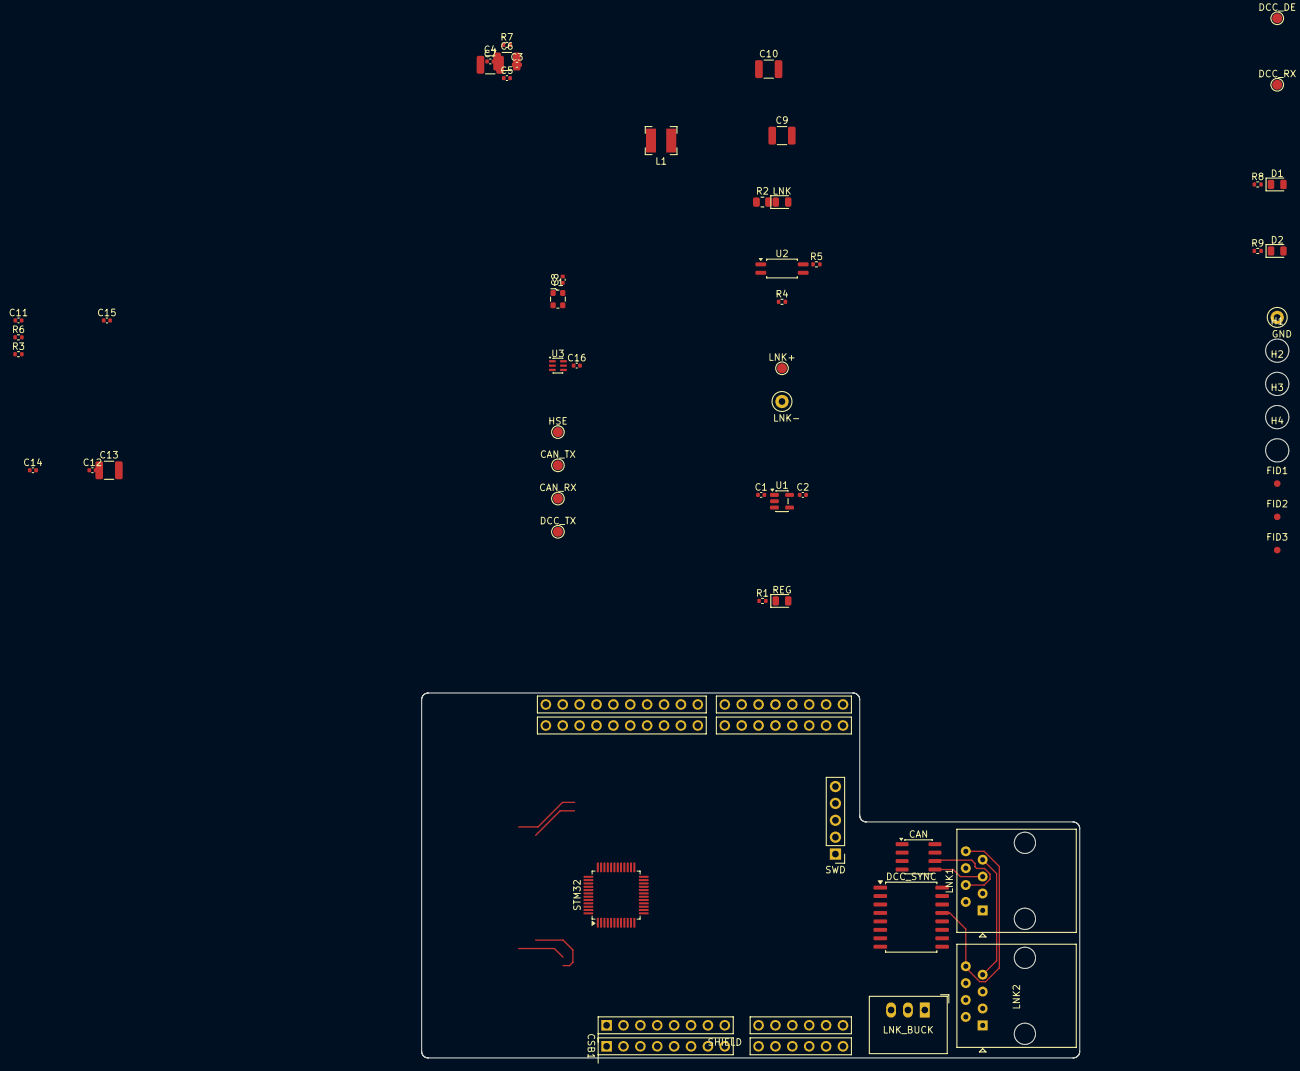
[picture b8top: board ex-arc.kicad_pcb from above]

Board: 2 copper layers, 99.0 x 54.9 mm, 59 parts (0 on the bottom side), 58 nets.

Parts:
C1, C2: 1µF; C_0402_1005Metric
C3, C5, C7, C8, C11, C12, C14, C15, C16: 100nF; C_0402_1005Metric
C4, C10, C13: 4.7µF; C_1210_3225Metric
C6: 1µF; C_1210_3225Metric
C9: 10µF; C_1210_3225Metric
CAN: ISO1044BD; SOIC-8_3.9x4.9mm_P1.27mm
CAN_RX: TestPoint; TestPoint_Pad_D1.5mm
CAN_TX: TestPoint; TestPoint_Pad_D1.5mm
CSB1: Arduino_UNO_R3; Arduino_UNO_R3_Pins
D1, D2: red; LED_0805_2012Metric
DCC_DE: TestPoint; TestPoint_Pad_D1.5mm
DCC_RX: TestPoint; TestPoint_Pad_D1.5mm
DCC_SYNC: ISO1430DW; SOIC-16W_7.5x10.3mm_P1.27mm
DCC_TX: TestPoint; TestPoint_Pad_D1.5mm
FID1, FID2, FID3: Fiducial; Fiducial_1mm_Mask2mm
GND: TestPoint; TestPoint_Loop_D2.50mm_Drill1.0mm
H1, H2, H3, H4: MountingHole; MountingHole_3.5mm
HSE: TestPoint; TestPoint_Pad_D1.5mm
L1: 15µH; L_Bourns-SRN4018
LNK: green; LED_0805_2012Metric
LNK1, LNK2: RJ45; RJ45_Amphenol_54602-x08_Horizontal
LNK+: TestPoint; TestPoint_Pad_D1.5mm
LNK-: TestPoint; TestPoint_Loop_D2.50mm_Drill1.0mm
LNK_BUCK: R-78E5.0-0.5; Converter_DCDC_RECOM_R-78E-0.5_THT
R1: 680Ω; R_0402_1005Metric
R2: 300Ω; R_0805_2012Metric
R3, R7: 10kΩ; R_0402_1005Metric
R4: 2kΩ; R_0402_1005Metric
R5: 100kΩ; R_0402_1005Metric
R6: 33Ω; R_0402_1005Metric
R8, R9: 620Ω; R_0402_1005Metric
REG: green; LED_0805_2012Metric
SHIELD: Arduino_UNO_R3; Arduino_UNO_R3_Socket
STM32: STM32C092CBTx; LQFP-48_7x7mm_P0.5mm
SWD: Conn_01x05; PinHeader_1x05_P2.54mm_Vertical
U1: AP2112K-3.3; SOT-23-5
U2: FODM217A; SOP-4_4.4x2.6mm_P1.27mm
U3: 74LVC1G3157; SOT-363_SC-70-6
Y1: 40MHz; Oscillator_SMD_ECS_2520MV-xxx-xx-4Pin_2.5x2.0mm

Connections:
3V3: C2.1, C3.1, C4.1, C6.1, C7.1, C8.1, C11.1, C14.1, C16.1, CAN.1, D1.2, D2.2, DCC_SYNC.1, R5.2, REG.2, STM32.5, STM32.6, SWD.4, U1.5, U3.5, Y1.1, Y1.4
unnamed: CSB1.9, SHIELD.9
unnamed: CSB1.10, SHIELD.10
unnamed: CSB1.11, SHIELD.11
unnamed: CSB1.12, SHIELD.12
unnamed: CSB1.30, SHIELD.30
unnamed: CSB1.15, SHIELD.15
unnamed: CSB1.16, SHIELD.16
unnamed: CSB1.17, SHIELD.17
unnamed: CSB1.18, SHIELD.18
unnamed: CSB1.19, SHIELD.19
unnamed: CSB1.20, SHIELD.20
unnamed: CSB1.21, SHIELD.21
unnamed: CSB1.25, SHIELD.25
unnamed: CSB1.26, SHIELD.26
unnamed: CSB1.28, SHIELD.28
unnamed: CSB1.2, SHIELD.2
unnamed: CSB1.4, SHIELD.4
unnamed: CSB1.32, SHIELD.32
unnamed: CSB1.31, SHIELD.31
unnamed: CSB1.8, SHIELD.8
unnamed: D1.1, R8.1
unnamed: D2.1, R9.1
unnamed: DCC_RX.1, R6.2, STM32.30, U3.1
unnamed: LNK.1, R2.1
unnamed: C10.1, L1.2, LNK_BUCK.1
unnamed: R1.1, REG.1
unnamed: R8.2, STM32.22
unnamed: R9.2, STM32.23
unnamed: R4.2, U2.1
booster/input: CSB1.22, SHIELD.22, U3.4
booster/select: R7.1, STM32.27, U3.6
brake/c: SHIELD.24, STM32.43
brake/d: SHIELD.23, STM32.44
dcc/de: DCC_DE.1, DCC_SYNC.5, R3.1, STM32.1
dcc/rxd: DCC_SYNC.3, R6.1
dcc/txd: CSB1.27, DCC_SYNC.6, DCC_TX.1, SHIELD.27
fault/c: SHIELD.13, STM32.45
fault/d: SHIELD.14, STM32.46
host/reset: CSB1.3, SHIELD.3, STM32.24
host/rxd: CSB1.14, STM32.13
host/txd: CSB1.13, STM32.14
host/v5.gnd: C1.2, C2.2, C3.2, C4.2, C5.2, C6.2, C7.2, C8.2, C11.2, C14.2, C16.2, CAN.4, CSB1.6, CSB1.7, CSB1.29, DCC_SYNC.2, DCC_SYNC.4, DCC_SYNC.8, GND.1, R1.2, R3.2, R7.2, SHIELD.6, SHIELD.7, SHIELD.29, STM32.7, SWD.5, U1.2, U2.3, U3.2, Y1.2
host/v5.rail: C1.1, CSB1.5, SHIELD.5, U1.1, U1.3
hse: HSE.1, STM32.8, Y1.3
link/V5_LINK: C12.1, C13.1, C15.1, CAN.8, DCC_SYNC.16, LNK.2, LNK+.1, LNK_BUCK.3, R4.1
link/VLINK: C9.1, L1.1, LNK1.1, LNK1.3, LNK2.1, LNK2.3
link/VLINK_GND: C9.2, C10.2, C12.2, C13.2, C15.2, CAN.7, DCC_SYNC.9, DCC_SYNC.15, LNK1.2, LNK1.6, LNK2.2, LNK2.6, LNK-.1, LNK_BUCK.2, R2.2, U2.2
link/fdcan.rx: CAN.3, CAN_RX.1, STM32.38
link/fdcan.tx: CAN.2, CAN_TX.1, STM32.39
link/good: R5.1, STM32.25, U2.4
link/jacks/CANH: CAN.6, LNK1.4, LNK2.4
link/jacks/CANL: CAN.5, LNK1.5, LNK2.5
link/jacks/DCC_A: DCC_SYNC.12, LNK1.7, LNK2.7
link/jacks/DCC_B: DCC_SYNC.13, LNK1.8, LNK2.8
swd/swd.nrst: C5.1, STM32.10, SWD.3
swd/swd.swclk: STM32.36, SWD.2
swd/swd.swdio: STM32.35, SWD.1
